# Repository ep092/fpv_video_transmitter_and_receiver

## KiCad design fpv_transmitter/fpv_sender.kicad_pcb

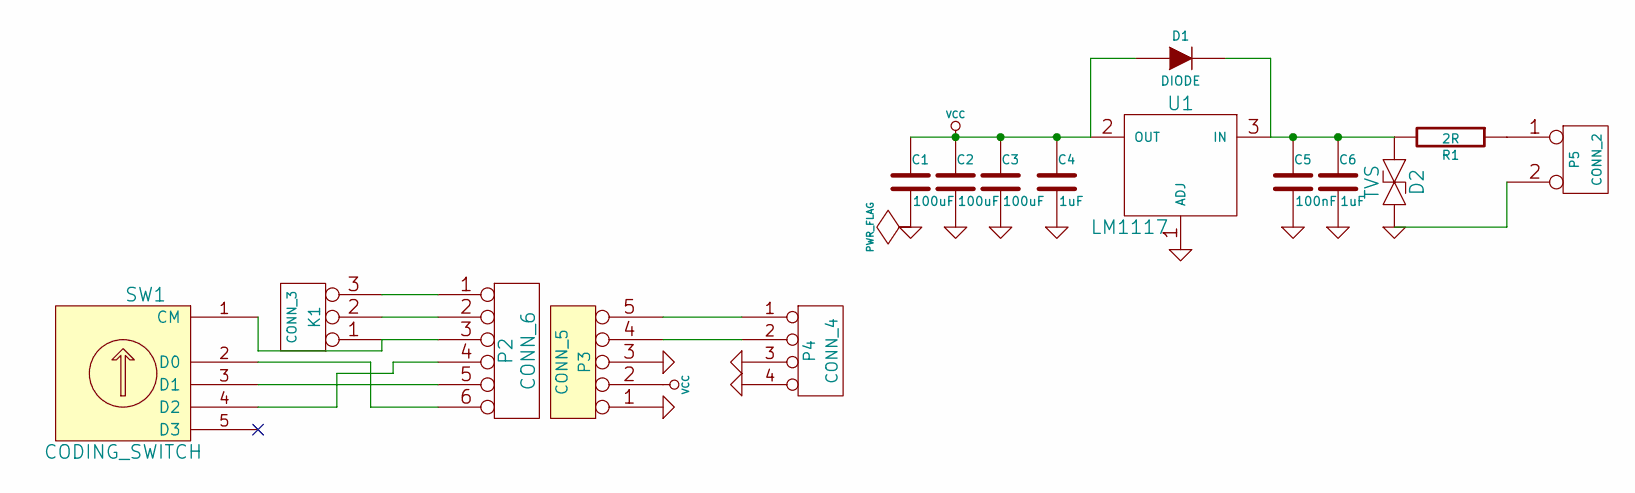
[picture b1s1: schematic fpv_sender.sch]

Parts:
C1, C2, C3: 100uF
C4, C6: 1uF
C5: 100nF
D1: DIODE
D2: TVS
K1: CONN_3
P2: CONN_6
P3: CONN_5
P4: CONN_4
P5: CONN_2
R1: 2R
SW1: CODING_SWITCH
U1: LM1117

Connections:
GND: C1.2, C2.2, C3.2, C4.2, C5.2, C6.2, D2.2, P3.1, P3.3, P4.3, P4.4, P5.2 (PM), U1.1 (ADJ)
unnamed: C5.1, C6.1, D1.2 (K), D2.1, R1.2, U1.3 (IN)
unnamed: K1.1, P2.3, SW1.1 (CM)
unnamed: K1.2 (PM), P2.2
unnamed: K1.3, P2.1
unnamed: P2.4, SW1.4 (D2)
unnamed: P2.5, SW1.3 (D1)
unnamed: P2.6, SW1.2 (D0)
unnamed: P3.4, P4.2
unnamed: P3.5, P4.1
unnamed: P5.1, R1.1
VCC: C1.1, C2.1, C3.1, C4.1, D1.1 (A), P3.2, U1.2 (OUT)

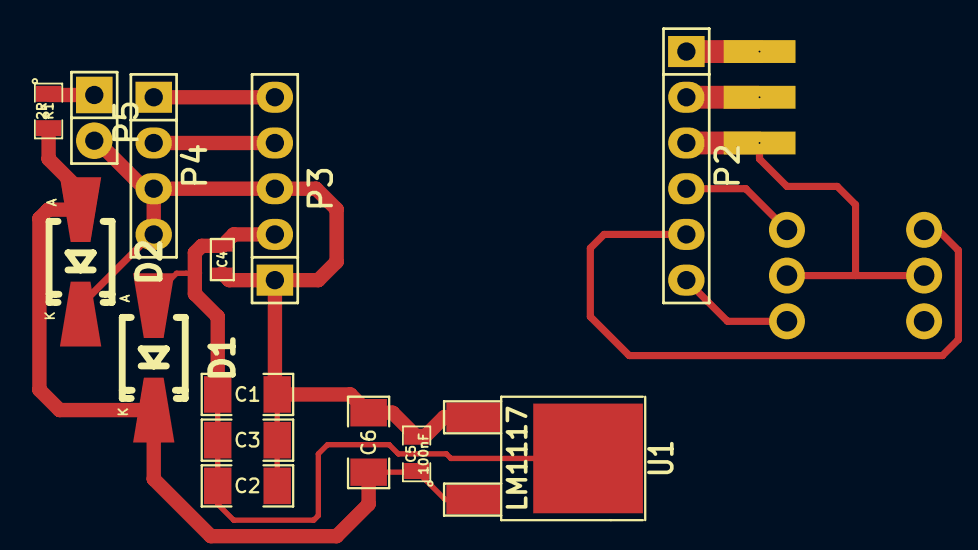
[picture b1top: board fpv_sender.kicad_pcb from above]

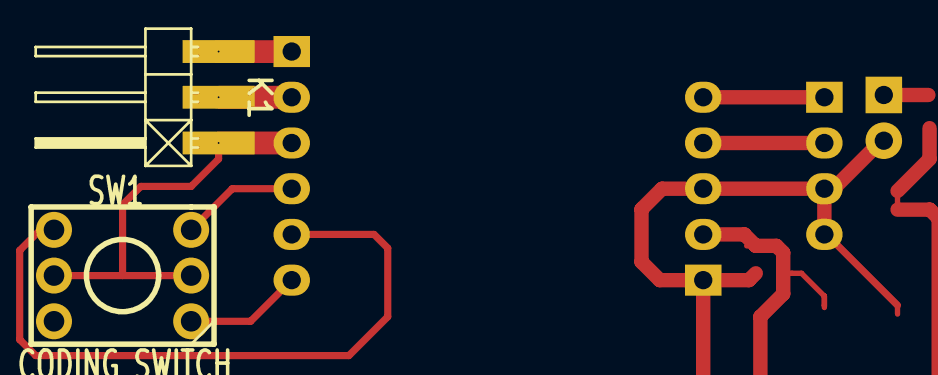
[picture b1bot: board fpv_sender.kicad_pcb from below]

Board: 2 copper layers, 16 parts (2 on the bottom side), 12 nets.

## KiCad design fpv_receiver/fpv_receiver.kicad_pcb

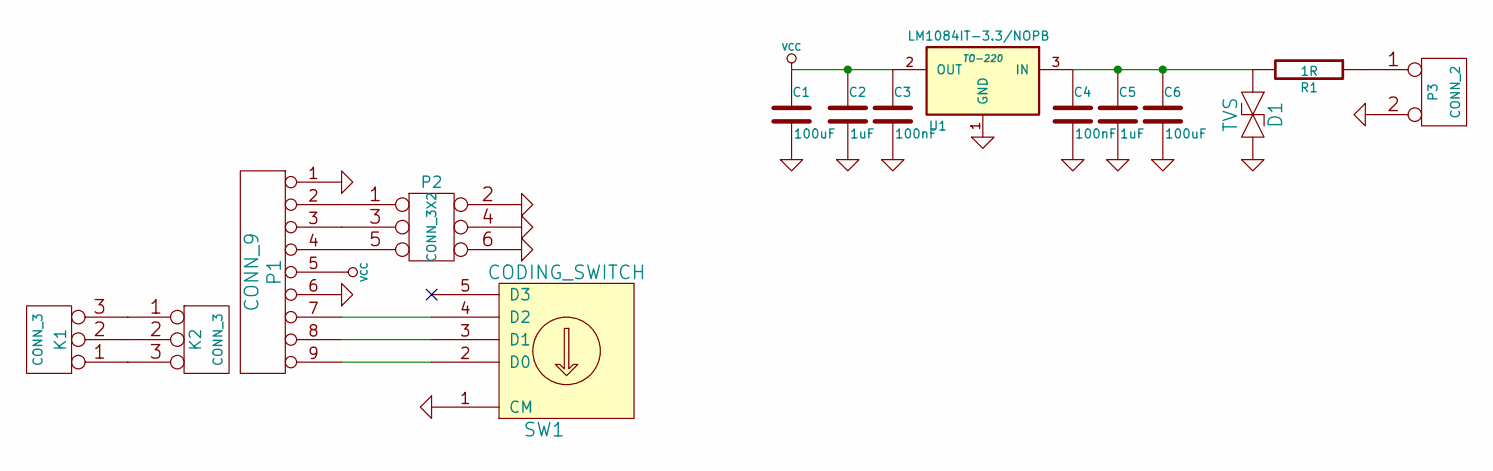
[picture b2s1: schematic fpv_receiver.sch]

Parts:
C1, C6: 100uF
C2, C5: 1uF
C3, C4: 100nF
D1: TVS
K1, K2: CONN_3
P1: CONN_9
P2: CONN_3X2
P3: CONN_2
R1: 1R
SW1: CODING_SWITCH
U1: LM1084IT-3.3/NOPB; TO-220

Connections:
GND: C1.2, C2.2, C3.2, C4.2, C5.2, C6.2, D1.2, P1.1, P1.6, P2.2, P2.4, P2.6, P3.2 (PM), SW1.1 (CM), U1.1 (GND)
unnamed: C4.1, C5.1, C6.1, D1.1, R1.2, U1.3 (IN)
unnamed: K1.1, K2.3
unnamed: K1.2 (PM), K2.2 (PM)
unnamed: K1.3, K2.1
unnamed: P1.2, P2.1
unnamed: P1.3, P2.3
unnamed: P1.4, P2.5
unnamed: P1.7, SW1.4 (D2)
unnamed: P1.8, SW1.3 (D1)
unnamed: P1.9, SW1.2 (D0)
unnamed: P3.1, R1.1
VCC: C1.1, C2.1, C3.1, P1.5, U1.2 (OUT)

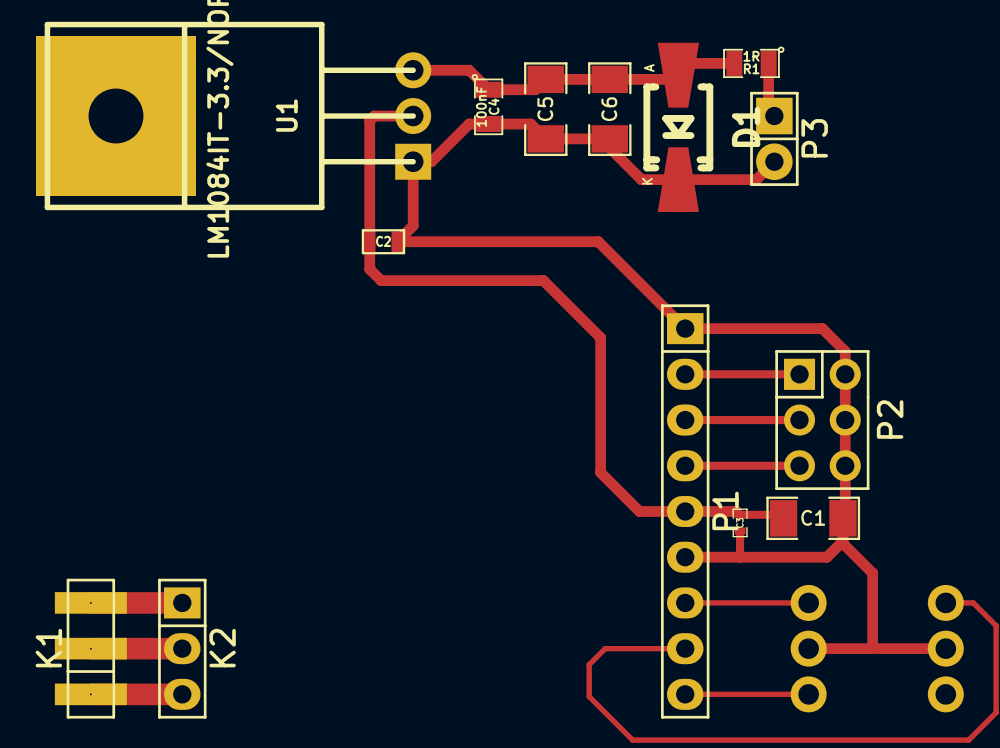
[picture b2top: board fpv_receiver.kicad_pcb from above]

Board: 2 copper layers, 15 parts (1 on the bottom side), 13 nets.
